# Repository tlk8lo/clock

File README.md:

# Timer

A school timer which displays time to the end of lesson/break. Uses [DCF77](https://en.wikipedia.org/wiki/DCF77) time signal for synchronization. Can also work as a typical digital clock. Since this is a project for our school, the documentation is written in Polish.

Szkolny timer wyświetlający czas do końca lekcji/przerwy. Używa sygnału radiowego [DCF77](https://en.wikipedia.org/wiki/DCF77) do synchronizacji czasu. Może również pracować jako normalny zegar cyfrowy.

## Budowa

Urządzenie składa się z mikrokontrolera AVR ATtiny24A, modułu odbiornika sygnału DCF77 oraz 2 układów SCT2024 sterujących 4 dużymi wyświetlaczami 7-segmentowymi. Posiada 4 przyciski do konfiguracji godzin lekcyjnych (zapisywanych w pamięci EEPROM). Wymaga zasilania prądem stałym o napięciu **15V** i pobiera maksymalnie **1,2A**. _Podczas montażu urządzenia, przewód zasilający należy poprowadzić jak najdalej od anteny, ponieważ powoduje on znaczne zakłócenia._

## Sposób działania

Po włączeniu zasilania, urządzenie czeka na odebranie poprawnej ramki DCF77 w celu synchronizacji czasu. Po udanej synchronizacji, wyświetla:

* Aktualną godzinę (jeżeli nie są zapisane żadne lekcje)
* Czas do końca przerwy (jeżeli trwa przerwa)
* Czas do końca lekcji (jeżeli trwa lekcja) - zapala się wtedy kropka po prawej stronie 4 cyfry

Kropka pomiędzy 2 i 3 cyfrą informuje o statusie synchronizacji:

* Jeżeli odebrano poprawną ramkę DCF77 w ciągu ostatnich 24 godzin - kropka świeci się
* W przeciwnym razie - kropka odzwierciedla stan odbiornika DCF77 (pozwala to wizualnie ocenić jakość odbieranego sygnału)

## Konfiguracja lekcji

W celu konfiguracji godzin lekcyjnych, należy nacisnąć dowolny przycisk, aby wejść do menu głównego.\
W menu, poszczególne przyciski umożliwiają nawigację, na zasadzie strzałek:

```
  ↑  
←   →
  ↓  
```

**Menu główne**

W menu głównym można ustawić godziny rozpoczęcia i zakończenia poszczególnych lekcji, a także dodawać i usuwać lekcje.\
Można dodać maksymalnie 32 lekcje.\
Jeżeli usunie się wszystkie lekcje, urządzenie działa jak zwyczajny zegar.

_Na poniższym przykładzie dodano 9 lekcji (od 00 do 08)._

```
                  ------------ Ustaw początek lekcji ------------         Dodaj nową lekcję          
                  ↑                 ↑                           ↑                 ↑                  
             ┌─────────┐       ┌─────────┐                 ┌─────────┐       ┌─────────┐             
Wyjdź    ←   │ 0 0   L │   ↔   │ 0 1   L │   ↔   ...   ↔   │ 0 8   L │   ↔   │ L A S T │   →   Wyjdź 
z menu       └─────────┘       └─────────┘                 └─────────┘       └─────────┘       z menu
                  ↓                 ↓                           ↓                 ↓                  
                  ------------- Ustaw koniec lekcji -------------        Usuń ostatnią lekcję        
```

**Menu ustawiania początku/końca lekcji**

To menu umożliwia zmianę godziny początku/końca danej lekcji.\
Kropka oznacza aktualnie edytowaną cyfrę.\
Domyślnie lekcja trwa 45 min, dlatego koniec lekcji jest ustawiany automatycznie. (Koniec lekcji można nadpisać ręcznie, wybierając "Ustaw koniec lekcji" w menu głównym.)

_Na poniższym przykładzie ustawiono godzinę 09:45._

```
               +                   +                   +                   +               
               ↑                   ↑                   ↑                   ↑               
             ┌─────────┐       ┌─────────┐       ┌─────────┐       ┌─────────┐             
Wróć do  ←   │ 0.9 4 5 │   ↔   │ 0 9.4 5 │   ↔   │ 0 9 4.5 │   ↔   │ 0 9 4 5.│   →  Wróć do
menu gł      └─────────┘       └─────────┘       └─────────┘       └─────────┘      menu gł
               ↓                   ↓                   ↓                   ↓               
               -                   -                   -                   -               
```

## Struktura repozytorium

* [src](src) - kod źródłowy programu mikrokontrolera
* [pcb](pcb) - schemat obwodu i projekt płytki PCB
* [cad](cad) - modele elementów obudowy
* [photos](photos) - zdjęcia gotowego urządzenia

## Licencja

[MIT](LICENSE)

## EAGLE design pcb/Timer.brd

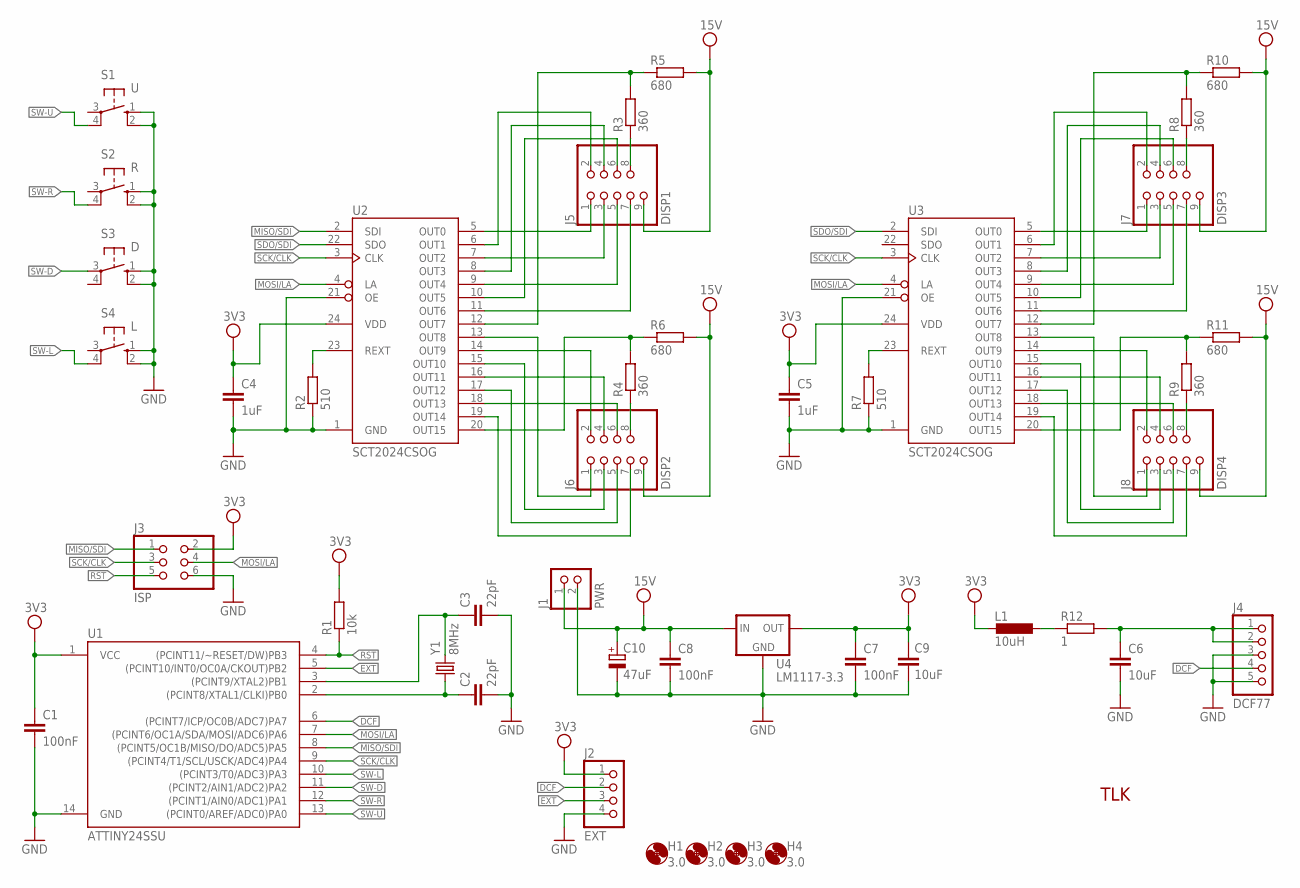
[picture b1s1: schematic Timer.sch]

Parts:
C1, C7, C8: 100nF; C0805
C2, C3: 22pF; C0805
C4, C5: 1uF; C0805
C6, C9: 10uF; C0805
C10: 47uF; E2,5
H1, H2, H3, H4: 3.0; 3,0
J1: PWR; 1X02/90
J2: EXT; 1X04/90
J3: ISP; 2X03/90
J4: DCF77; 1X05/90
J5: DISP1; 2X04/05/90
J6: DISP2; 2X04/05/90
J7: DISP3; 2X04/05/90
J8: DISP4; 2X04/05/90
L1: 10uH; L0805
R1: 10k; R0805
R2, R7: 510; R0805
R3, R4, R8, R9: 360; R1206
R5, R6, R10, R11: 680; R1206
R12: 1; R0805
S1: U; TACT-12
S2: R; TACT-12
S3: D; TACT-12
S4: L; TACT-12
U1: ATTINY24SSU; SO14
U2, U3: SCT2024CSOG; SO24W
U4: LM1117-3.3; SOT223
Y1: 8MHz; HC49UP

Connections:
DCF: J2.2, J4.4, U1.6 ((PCINT7/ICP/OC0B/ADC7)PA7)
EXT: J2.3, U1.5 ((PCINT10/INT0/OC0A/CKOUT)PB2)
GND: C1.2, C2.2, C3.2, C4.2, C5.2, C6.2, C7.2, C8.2, C9.2, C10.-, J1.2, J2.4, J3.6, J4.3, J4.5, R2.1, R7.1, S1.1 (S), S1.2 (S1), S2.1 (S), S2.2 (S1), S3.1 (S), S3.2 (S1), S4.1 (S), S4.2 (S1), U1.14 (GND), U2.1 (GND), U2.21 (OE), U3.1 (GND), U3.21 (OE), U4.1 (GND)
MISO/SDI: J3.1, U1.8 ((PCINT5/OC1B/MISO/DO/ADC5)PA5), U2.2 (SDI)
MOSI/LA: J3.4, U1.7 ((PCINT6/OC1A/SDA/MOSI/ADC6)PA6), U2.4 (LA), U3.4 (LA)
unnamed: C3.1, U1.3 ((PCINT9/XTAL2)PB1), Y1.2
unnamed: C2.1, U1.2 ((PCINT8/XTAL1/CLKI)PB0), Y1.1
unnamed: C6.1, J4.1, J4.2, R12.2
unnamed: J5.1, U2.5 (OUT0)
unnamed: J5.2, U2.6 (OUT1)
unnamed: J5.3, U2.7 (OUT2)
unnamed: J5.4, U2.8 (OUT3)
unnamed: J5.5, U2.9 (OUT4)
unnamed: J5.6, U2.10 (OUT5)
unnamed: J5.8, R3.1
unnamed: J5.7, U2.11 (OUT6)
unnamed: R3.2, R5.1, U2.12 (OUT7)
unnamed: J6.2, U2.14 (OUT9)
unnamed: J7.1, U3.5 (OUT0)
unnamed: J7.3, U3.7 (OUT2)
unnamed: J7.5, U3.9 (OUT4)
unnamed: J7.7, U3.11 (OUT6)
unnamed: J7.2, U3.6 (OUT1)
unnamed: J7.4, U3.8 (OUT3)
unnamed: J7.6, U3.10 (OUT5)
unnamed: J7.8, R8.1
unnamed: J6.4, U2.16 (OUT11)
unnamed: R8.2, R10.1, U3.12 (OUT7)
unnamed: J8.2, U3.14 (OUT9)
unnamed: J8.4, U3.16 (OUT11)
unnamed: J8.6, U3.18 (OUT13)
unnamed: R9.2, R11.1, U3.20 (OUT15)
unnamed: J8.8, R9.1
unnamed: L1.1, R12.1
unnamed: J8.1, U3.13 (OUT8)
unnamed: J8.3, U3.15 (OUT10)
unnamed: J8.5, U3.17 (OUT12)
unnamed: J6.6, U2.18 (OUT13)
unnamed: J6.8, R4.1
unnamed: J6.7, U2.19 (OUT14)
unnamed: J6.5, U2.17 (OUT12)
unnamed: R7.2, U3.23 (REXT)
unnamed: R2.2, U2.23 (REXT)
unnamed: J6.3, U2.15 (OUT10)
unnamed: J6.1, U2.13 (OUT8)
unnamed: R4.2, R6.1, U2.20 (OUT15)
unnamed: J8.7, U3.19 (OUT14)
RST: J3.5, R1.1, U1.4 ((PCINT11/~RESET/DW)PB3)
SCK/CLK: J3.3, U1.9 ((PCINT4/T1/SCL/USCK/ADC4)PA4), U2.3 (CLK), U3.3 (CLK)
SDO/SDI: U2.22 (SDO), U3.2 (SDI)
SW-D: S3.3, U1.11 ((PCINT2/AIN1/ADC2)PA2)
SW-L: S4.4 (P1), U1.10 ((PCINT3/T0/ADC3)PA3)
SW-R: S2.4 (P1), U1.12 ((PCINT1/AIN0/ADC1)PA1)
SW-U: S1.4 (P1), U1.13 ((PCINT0/AREF/ADC0)PA0)
VCC: C1.1, C4.1, C5.1, C7.1, C9.1, J2.1, J3.2, L1.2, R1.2, U1.1 (VCC), U2.24 (VDD), U3.24 (VDD), U4.2 (OUT), U4.4 (OUT)
VDD: C8.1, C10.+, J1.1, J5.9, J6.9, J7.9, J8.9, R5.2, R6.2, R10.2, R11.2, U4.3 (IN)

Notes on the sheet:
TLK

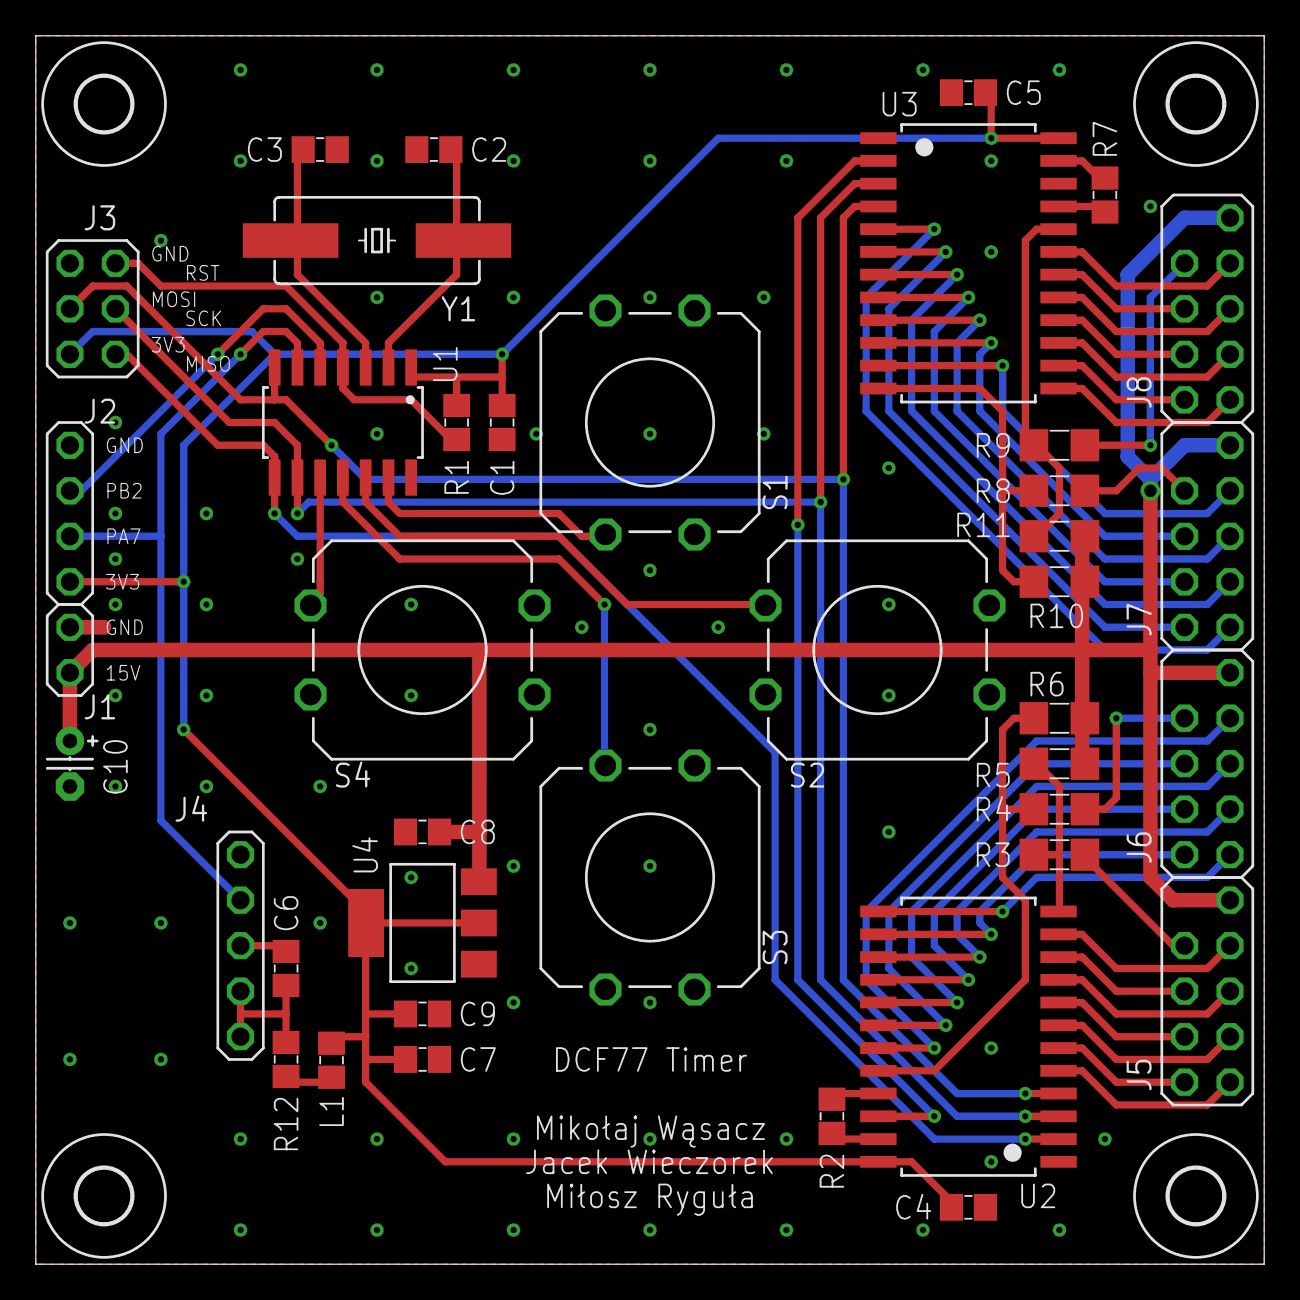
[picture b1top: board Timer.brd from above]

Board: 2 copper layers, 68.6 x 68.6 mm, 44 parts (0 on the bottom side), 56 nets.

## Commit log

2019-10-16 Add BOM
2019-11-11 Add schematic and preliminary pcb layout
2019-12-01 Add Extension connector, move some traces
2019-12-02 Add ground planes
2019-12-17 Add CAD models
2020-01-28 Update 'dystans'
2020-03-08 Update footprints and silkscreen
2020-04-05 Fix errors, move components to a common library
2020-04-05 Change C6 value
2020-04-05 Add Gerber files
2020-06-28 Add source code
2020-06-28 Create LICENSE
2020-06-28 Add missing `static` specifier
    See: https://stackoverflow.com/questions/16245521/c99-inline-function-in-c-file/16245669#16245669
2020-06-28 Add missing `extern` specifier
2020-06-28 Add simple makefile
2020-06-29 Add more missing static specifiers
2020-06-29 Change load_display() to macro for better optimization
2020-09-02 Add photos
2020-09-14 Change device to ATtiny24A
2020-09-17 Fix bugs, add option to set current time
2020-09-21 Revert "Fix bugs, add option to set current time"
    This reverts commit 75b06e3f8055a057145ca035266ad130e721dde4.
2020-09-22 Add DCF signal indicator, fix minor bugs
